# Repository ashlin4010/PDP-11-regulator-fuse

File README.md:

# PDP-11 Regulator Fuse  Board

This is a little fuse board that goes between the DEC h744 and h745.
Both of these regulator modules do not contain any fuses on the AC input, if for example the bridge rectifier fails then the traces on the regulator will explode 💥, that's rather annoying and destructive so this borders to adds a fuse.

Later generation modules shuch as the H7441 include a 32V 15A fuse. 

## BOM
 * 1x [Fuse Cap](https://www.aliexpress.com/item/4000810342695.html) (6*30mm PCB Fuse Holder Cover Fuse Clip)
 * 2x [Fuse Holder](https://www.digikey.co.nz/en/products/detail/eaton-electronics-division/BK-1A1907-06-R/954119)
 * 1x [Fuse 32V 15A](https://www.digikey.co.nz/en/products/detail/littelfuse-inc/0AGC015-V/2519096)
 * 8x [Female Power Pins](https://www.digikey.co.nz/en/products/detail/te-connectivity-amp-connectors/61314-1/290258)
 * 8x [Male Power Pins](https://www.digikey.co.nz/en/products/detail/te-connectivity-amp-connectors/61116-1/290257)
 * Solid Core 16 AWG Wire
 * 1x [3D Printed Stand](https://www.tinkercad.com/things/0jvjAKjBNhU-pdp-fuse-stand)

### Power Connectors

The power connectors can be downloaded as [STL files](https://so-much-stuff.com/pdp8/cad/3d.php) and printed. JLCPCB's resin printing service does a really good job at printing them and cost about $1.50 each. 

Or you can buy them from here, minimum order quantity is 12:
 * https://www.connectorpeople.com/Connector/TYCO-AMP-TE_CONNECTIVITY/1/1-480460-0
 * https://www.connectorpeople.com/Connector/TYCO-AMP-TE_CONNECTIVITY/1/1-480459-0

## Images

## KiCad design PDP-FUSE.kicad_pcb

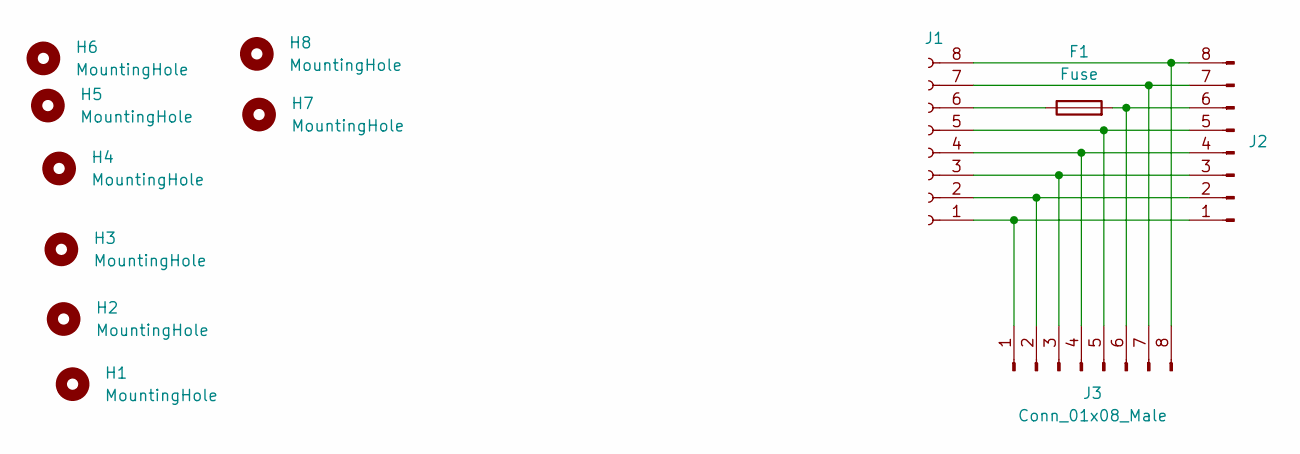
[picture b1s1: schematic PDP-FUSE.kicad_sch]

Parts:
F1: Fuse; Fuseholder_Clip-6.3x32mm_Littelfuse_102_122_Inline_P34.21x7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
H1, H2, H3, H4, H5, H6, H7, H8: MountingHole; MountingHole_3.2mm_M3
J1: Conn_01x08_Female; AMP-1-480459-0
J2: Conn_01x08_Male; AMP-1-480460-0
J3: Conn_01x08_Male; PinSocket_1x08_P2.54mm_Vertical

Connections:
unnamed: J1.1, J2.1, J3.1
unnamed: J1.2, J2.2, J3.2
unnamed: J1.3, J2.3, J3.3
unnamed: J1.4, J2.4, J3.4
unnamed: J1.5, J2.5, J3.5
unnamed: F1.1, J1.6
unnamed: J1.7, J2.7, J3.7
unnamed: J1.8, J2.8, J3.8
unnamed: F1.2, J2.6, J3.6

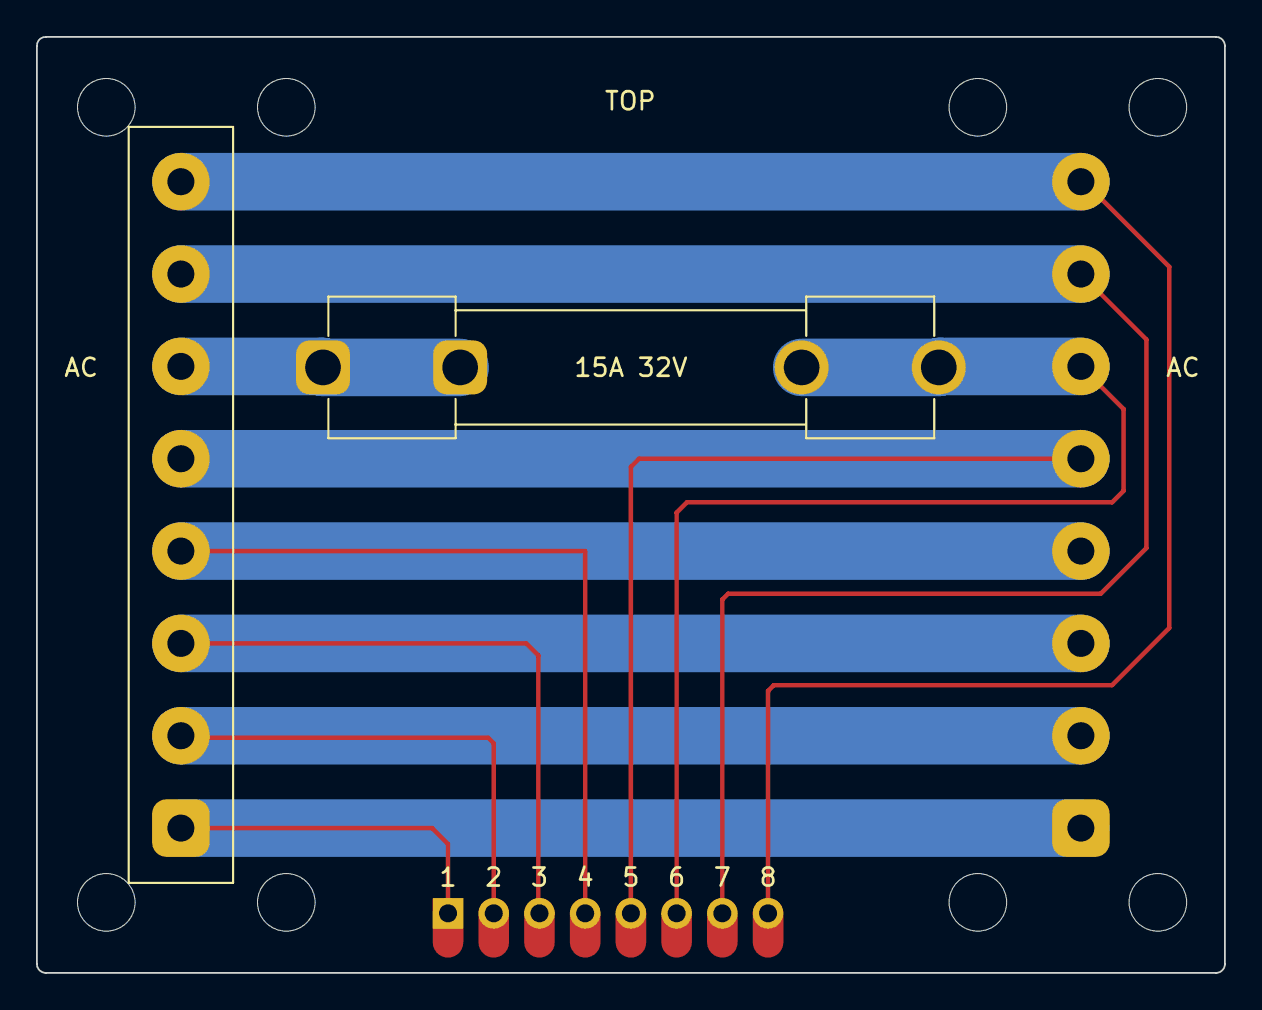
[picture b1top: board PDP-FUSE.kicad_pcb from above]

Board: 2 copper layers, 66.0 x 52.0 mm, 12 parts (1 on the bottom side), 9 nets.

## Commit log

2024-05-30 Typo
